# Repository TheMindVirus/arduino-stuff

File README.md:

# arduino-stuff
Miscellaneous Arduino Scripts for various tasks \
More Information: https://www.arduino.cc/

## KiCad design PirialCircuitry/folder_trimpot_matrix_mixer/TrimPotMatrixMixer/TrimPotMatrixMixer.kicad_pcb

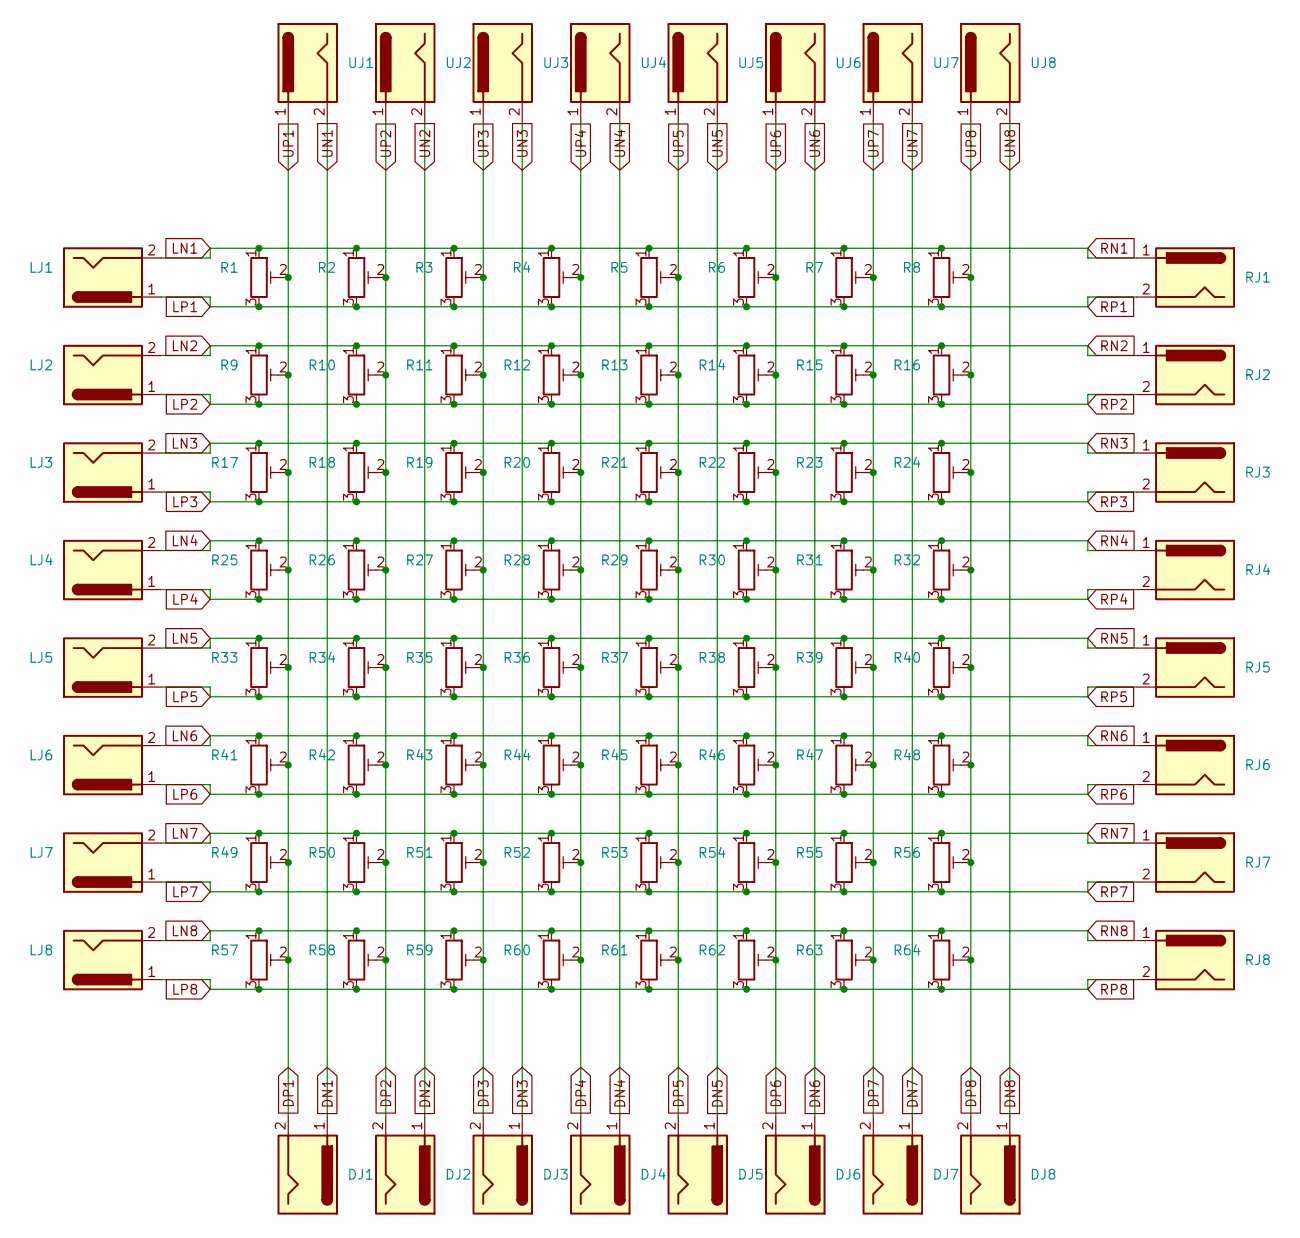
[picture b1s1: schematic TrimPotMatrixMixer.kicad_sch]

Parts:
DJ1, DJ2, DJ3, DJ4, DJ5, DJ6, DJ7, DJ8: Jack-DC; PinHeader_1x02_P2.54mm_Horizontal
LJ1, LJ2, LJ3, LJ4, LJ5, LJ6, LJ7, LJ8: Jack-DC; PinHeader_1x02_P2.54mm_Horizontal
R1, R2, R3, R4, R5, R6, R7, R8, R9, R10, R11, R12, R13, R14, R15, R16, R17, R18, R19, R20, R21, R22, R23, R24, R25, R26, R27, R28, R29, R30, R31, R32, R33, R34, R35, R36, R37, R38, R39, R40, R41, R42, R43, R44, R45, R46, R47, R48, R49, R50, R51, R52, R53, R54, R55, R56, R57, R58, R59, R60, R61, R62, R63, R64: R_Potentiometer_Trim; Potentiometer_ACP_CA9-V10_Vertical_Hole
RJ1, RJ2, RJ3, RJ4, RJ5, RJ6, RJ7, RJ8: Jack-DC; PinHeader_1x02_P2.54mm_Horizontal
UJ1, UJ2, UJ3, UJ4, UJ5, UJ6, UJ7, UJ8: Jack-DC; PinHeader_1x02_P2.54mm_Horizontal

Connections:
LP1: LJ1.1, R1.3, R2.3, R3.3, R4.3, R5.3, R6.3, R7.3, R8.3, RJ1.2
LP2: LJ2.1, R9.3, R10.3, R11.3, R12.3, R13.3, R14.3, R15.3, R16.3, RJ2.2
LP3: LJ3.1, R17.3, R18.3, R19.3, R20.3, R21.3, R22.3, R23.3, R24.3, RJ3.2
LP4: LJ4.1, R25.3, R26.3, R27.3, R28.3, R29.3, R30.3, R31.3, R32.3, RJ4.2
LP5: LJ5.1, R33.3, R34.3, R35.3, R36.3, R37.3, R38.3, R39.3, R40.3, RJ5.2
LP6: LJ6.1, R41.3, R42.3, R43.3, R44.3, R45.3, R46.3, R47.3, R48.3, RJ6.2
LP7: LJ7.1, R49.3, R50.3, R51.3, R52.3, R53.3, R54.3, R55.3, R56.3, RJ7.2
LP8: LJ8.1, R57.3, R58.3, R59.3, R60.3, R61.3, R62.3, R63.3, R64.3, RJ8.2
RN1: LJ1.2, R1.1, R2.1, R3.1, R4.1, R5.1, R6.1, R7.1, R8.1, RJ1.1
RN2: LJ2.2, R9.1, R10.1, R11.1, R12.1, R13.1, R14.1, R15.1, R16.1, RJ2.1
RN3: LJ3.2, R17.1, R18.1, R19.1, R20.1, R21.1, R22.1, R23.1, R24.1, RJ3.1
RN4: LJ4.2, R25.1, R26.1, R27.1, R28.1, R29.1, R30.1, R31.1, R32.1, RJ4.1
RN5: LJ5.2, R33.1, R34.1, R35.1, R36.1, R37.1, R38.1, R39.1, R40.1, RJ5.1
RN6: LJ6.2, R41.1, R42.1, R43.1, R44.1, R45.1, R46.1, R47.1, R48.1, RJ6.1
RN7: LJ7.2, R49.1, R50.1, R51.1, R52.1, R53.1, R54.1, R55.1, R56.1, RJ7.1
RN8: LJ8.2, R57.1, R58.1, R59.1, R60.1, R61.1, R62.1, R63.1, R64.1, RJ8.1
UN1: DJ1.1, UJ1.2
UN2: DJ2.1, UJ2.2
UN3: DJ3.1, UJ3.2
UN4: DJ4.1, UJ4.2
UN5: DJ5.1, UJ5.2
UN6: DJ6.1, UJ6.2
UN7: DJ7.1, UJ7.2
UN8: DJ8.1, UJ8.2
UP1: DJ1.2, R1.2, R9.2, R17.2, R25.2, R33.2, R41.2, R49.2, R57.2, UJ1.1
UP2: DJ2.2, R2.2, R10.2, R18.2, R26.2, R34.2, R42.2, R50.2, R58.2, UJ2.1
UP3: DJ3.2, R3.2, R11.2, R19.2, R27.2, R35.2, R43.2, R51.2, R59.2, UJ3.1
UP4: DJ4.2, R4.2, R12.2, R20.2, R28.2, R36.2, R44.2, R52.2, R60.2, UJ4.1
UP5: DJ5.2, R5.2, R13.2, R21.2, R29.2, R37.2, R45.2, R53.2, R61.2, UJ5.1
UP6: DJ6.2, R6.2, R14.2, R22.2, R30.2, R38.2, R46.2, R54.2, R62.2, UJ6.1
UP7: DJ7.2, R7.2, R15.2, R23.2, R31.2, R39.2, R47.2, R55.2, R63.2, UJ7.1
UP8: DJ8.2, R8.2, R16.2, R24.2, R32.2, R40.2, R48.2, R56.2, R64.2, UJ8.1

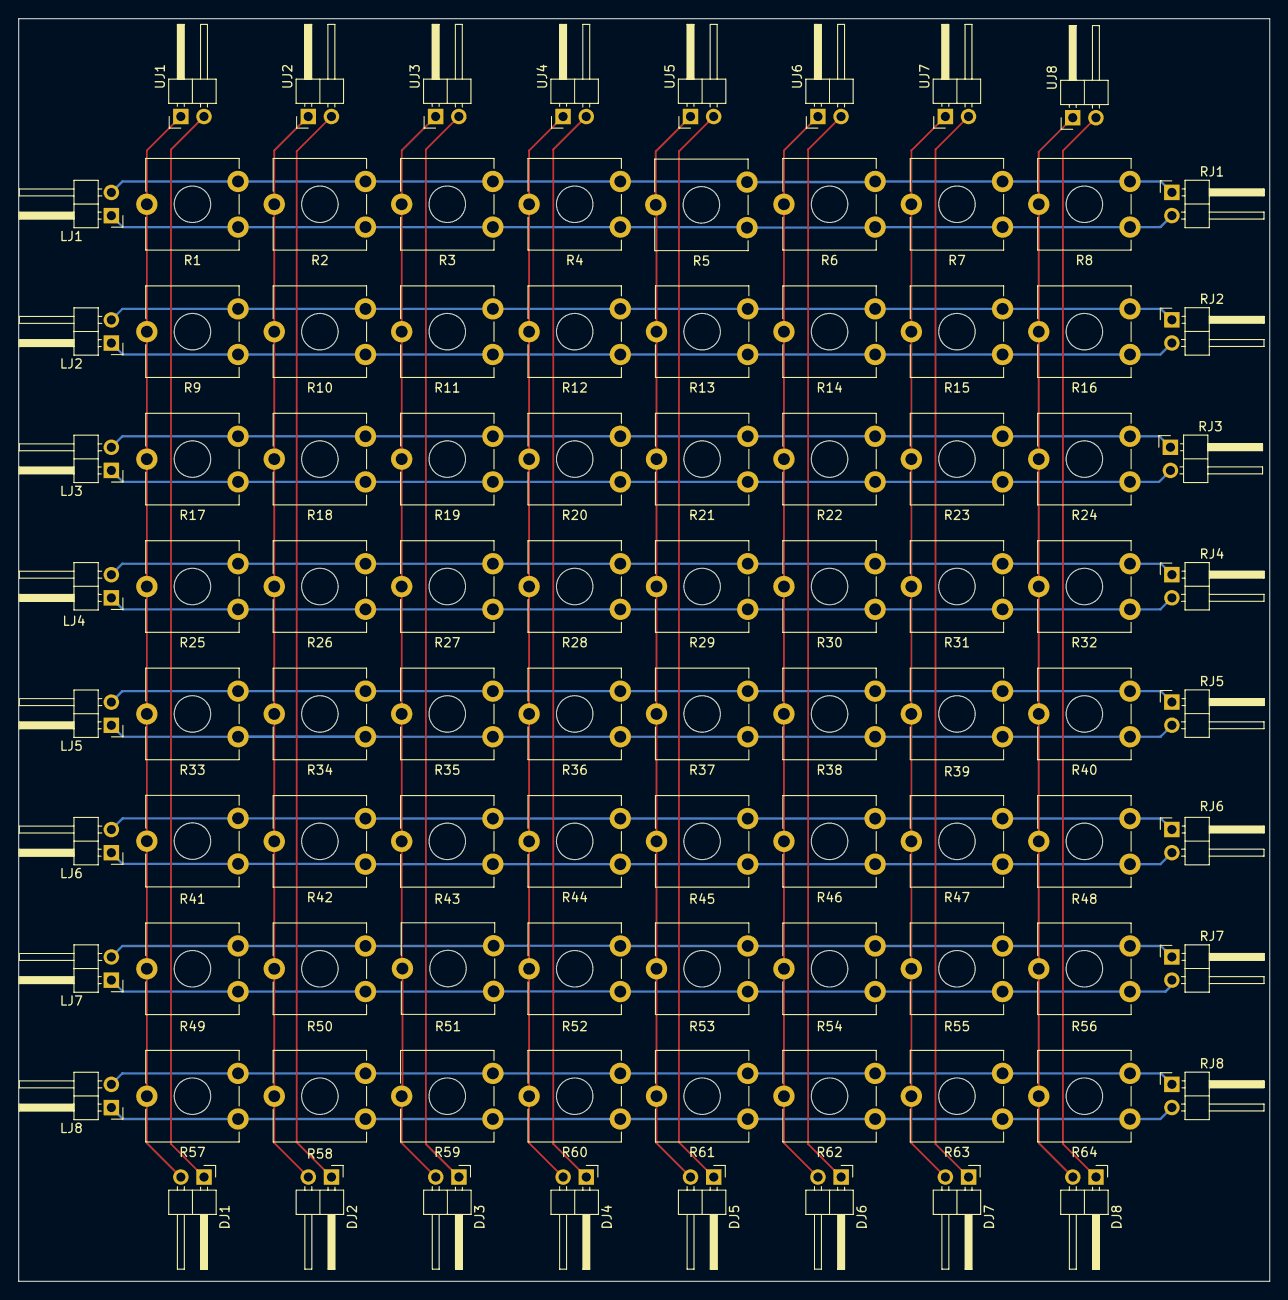
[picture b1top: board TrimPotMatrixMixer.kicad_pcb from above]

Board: 2 copper layers, 137.2 x 138.4 mm, 96 parts (0 on the bottom side), 32 nets.

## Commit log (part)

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2023-03-17 Move Arduino Lua to Whistles Dev
2023-05-05 Ported iomap to arduino
2023-05-17 Standardised W3BIOS
2023-06-02 Tested Redline_VCC Edge Networking
2023-06-02 Added devlog for Riser
2023-06-02 (File) Added devlog for Riser_mod
2023-09-03 Randomiser Vindication
2023-09-03 Uno On Uno
2023-09-29 Made Prototype CableJack
2023-10-10 Magic Shift Register Staple Board
    ATtiny45, 2x SN74HC595
2023-11-06 Ported tube map to arduino (not dma)
2023-11-07 Ported Tokyo Subway to Arduino
2023-11-18 VK_IOMAP_TUBE_VICINITY
2024-01-20 Zener Diode Bridge Rectifier
    Zener Diode Bridge Rectifier
2024-01-20 Componentry Symbols
2024-01-20 Componentry Kiro
    Kiro - キロ
    Omen of perfection seeking
    Precise Composition and Neatly Arranged Layout of the Parts of a Design that are due for Assembly
2024-01-20 Componentry Kiro
2024-02-03 Bugfix for 50/50 32s Timer Failure
2024-02-05 Benzene Rectifier
2024-02-05 Benzene Rectifier
    Benzener Rectifier
2024-02-05 Benzene Rectifier
    Benzener Rectifier
    Reed Relay Memristor
2024-02-05 Benzene Rectifier
    Benzener Rectifier
    Reed Relay Memristor
    Charge Direction Detector
2024-02-05 Resistive Memory
2024-02-05 Reed Relay
2024-02-05 MOSFET SR-Latch
2024-02-20 Resistor Ladder
2024-02-23 Reed Relay API
2024-02-23 || \\/\\//\// || BULKHEAD || \\/\\//\// ||
    || MODUINO || MOD || NEOPIXEL || TILE || BULKHEAD || \/\/\/ ||
2024-02-24 LED_BUILTIN_DIMMER
2024-02-24 || BULKHEAD_FLANGER ||
2024-02-25 Splay
2024-02-27 PirialCircuitry
2024-02-27 Pirial Circuitry
    Pyrial Componentry
2024-02-28 Pirial Circuitry
    Pyrial Componentry
    Pyroclastic Addenda
2024-02-28 Pirial Circuitry
    Pyrial Componentry
    Pyroclastic Addenda
    Ground Loop Isolator
2024-02-28 PirialCircuitry
    Pyrial Componentry
    Pyroclastic Addenda
    Ground Loop Isolator
    Mosfet Floating Gate
2024-02-29 ECGBeepTonePulse
2024-02-29 Protoduino\Veroduino
2024-02-29 Protoduino\Veroduino
    Some Assembly Required...
2024-03-01 Pirial Circuitry
    Pyrial Componentry
    Pyroclastic Addenda
    Ground Loop Isolator
    Mosfet Floating Gate
    Granular Audio Processor
2024-03-02 Pirial Circuitry
    Pyrial Componentry
    Pyroclastic Addenda
    Ground Loop Isolator
    Mosfet Floating Gate
    Granular Audio Processor
    Residual Current Devices
2024-03-02 Transformer Proximity
2024-03-03 Multiplexer Latcher
2024-03-04 PirialCircuitry
    Pyrial Componentry
    Pyroclastic Addenda
    Ground Loop Isolator
    Mosfet Floating Gate
    Granular Audio Processor
    Residual Current Devices
2024-03-05 Pirial Circuitry
    Pyrial Componentry
    Pyroclastic Addenda
    Ground Loop Isolator
    Mosfet Floating Gate
    Granular Audio Processor
    Residual Current Devices
2024-03-05 PirialCircuitry
    Pyrial Componentry
    Pyroclastic Addenda
    Ground Loop Isolator
    Mosfet Floating Gate
    Granular Audio Processor
    Residual Current Devices
2024-03-05 Pirial Circuitry
    Pyrial Componentry
    Pyroclastic Addenda
    Ground Loop Isolator
    Mosfet Floating Gate
    Granular Audio Processor
    Residual Current Devices
2024-03-11 PirialCircuitry
    Pyrial Componentry
    Pyroclastic Addenda
    Ground Loop Isolator
    Mosfet Floating Gate
    Granular Audio Processor
    Residual Current Devices
2024-03-11 MIDIbaud
2024-03-12 Pirial Circuitry
    Pyrial Componentry
    Pyroclastic Addenda
    Ground Loop Isolator
    Mosfet Floating Gate
    Granular Audio Processor
    Residual Current Devices
2024-03-15 PirialCircuitry
    Pyrial Componentry
    Pyroclastic Addenda
    Ground Loop Isolator
    Mosfet Floating Gate
    Granular Audio Processor
    Residual Current Devices
2024-03-16 FlowStone Derectifier
2024-03-16 Pirial Circuitry
    Pyrial Componentry
    Pyroclastic Addenda
    Ground Loop Isolator
    Mosfet Floating Gate
    Granular Audio Processor
    Residual Current Devices
2024-03-17 Miscellaneous
2024-04-02 Audio Buffer Modding
2024-04-04 Avalanche Diode
2024-05-23 Intel AMT IOCTL FW
    AMD DASH PTHI IPMI
2024-10-12 playstation_dualshock.py
2024-12-25 Dot Matrix Display
2024-12-26 Dot Matrix Display Parola
2024-12-26 Dot Matrix Display Parola Intensity
2024-12-27 Dot Matrix Display Parola Intensity ST77XX
2025-02-21 Hyper Threading
